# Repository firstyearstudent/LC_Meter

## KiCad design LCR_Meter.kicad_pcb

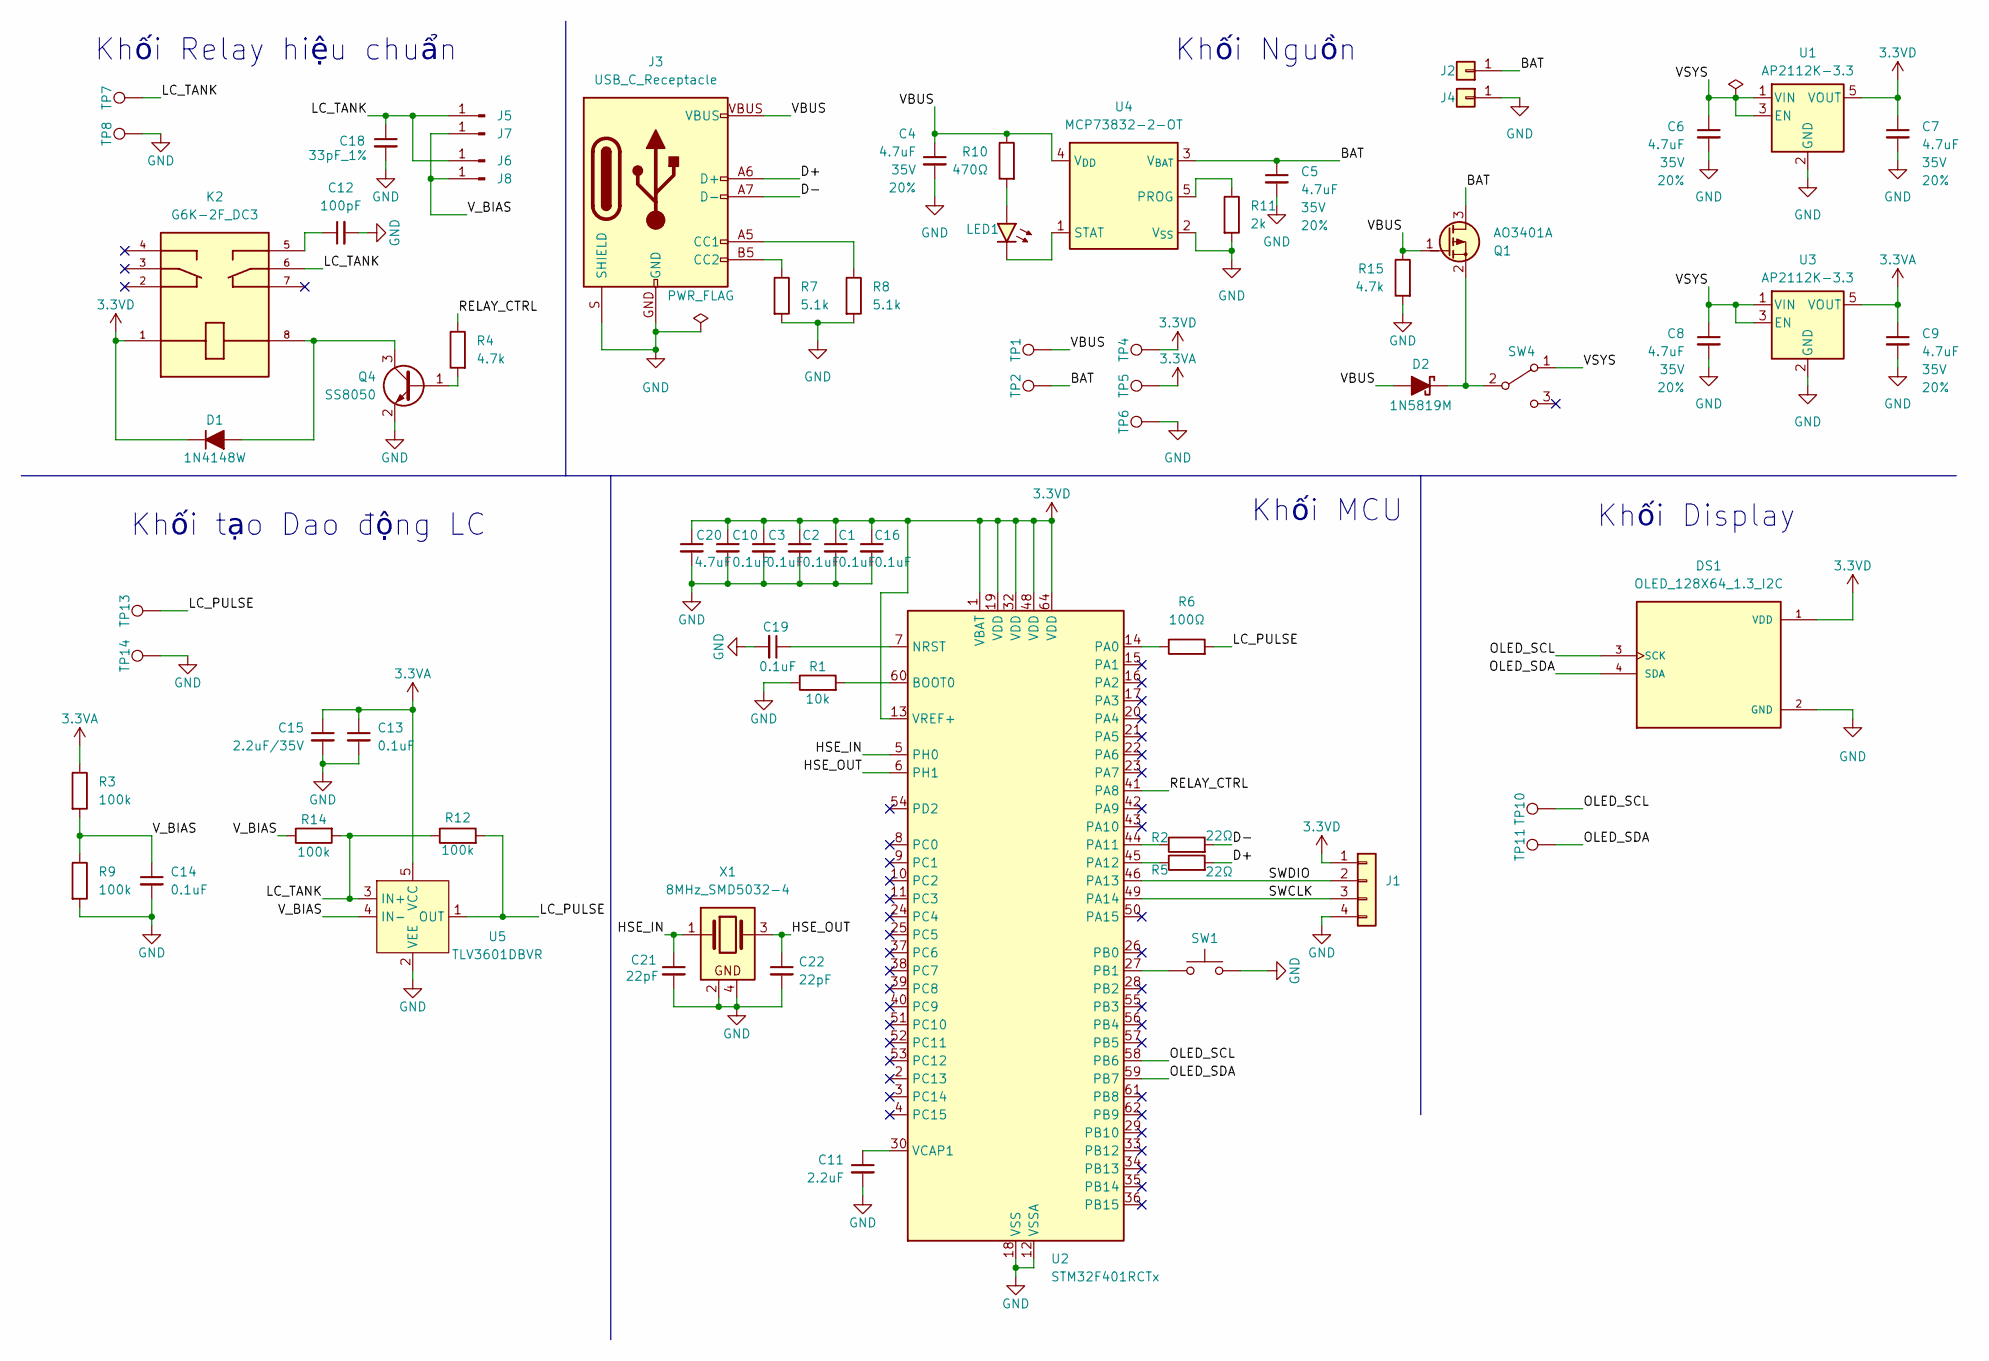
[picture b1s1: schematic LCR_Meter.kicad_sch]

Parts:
C1, C2, C3, C10, C13, C14, C16, C19: 100nF_0603_16V; C_0603; Part Number 0603YC104KAT2A; JLCPCB ID C14663
C4, C5, C6, C7, C8, C9: 4.7uF; C_0603_1608Metric; Voltage 35V; Tolerance 20%
C11: 2.2uF_0603_25V; C_0603; Part Number GRM188R6YA225KA12D; JLCPCB ID C57895
C12: 100pF_1%; C_0603; Part Number CC0603JRNPO9BN101; JLCPCB ID C14858
C15: 2.2uF_0805_35V; C_0805; Part Number GRT21BC8YA225KE13L; JLCPCB ID C49217
C18: 33pF_1%; C_0603_1608Metric
C20: 4.7uF_0603_10V; C_0603; Part Number CL10A475KP8NNNC; JLCPCB ID C1705
C21, C22: 22pF; C_0402_1005Metric
D1: 1N4148W; D_SOD-123
D2: 1N5819M; D_MELF
DS1: OLED_128X64_1.3_I2C; LCD_OLED_128X64_1.3_I2C; PARTREV NA
J1: PinHeader_1x04_P2.54mm_Vertical; Part Number TBD
J2, J4: Conn_01x01; SolderWire-0.75sqmm_1x01_D1.25mm_OD2.3mm
J3: USB_C_Receptacle; USB-C_16
J5, J7: Conn_01x01_Pin; SolderWirePad_1x01_SMD_2x4mm
J6, J8: Conn_01x01_Pin; Banana_Jack_1Pin
K2: G6K-2F_DC3; RELAY_G6K-2F_DC3; PARTREV K106-E1-11
LED1: LED_0805_Red; LED_0805_2012Metric
Q1: AO3401A; SOT-23
Q4: SS8050; SOT-23
R1: 10k_0603; R_0603; Part Number RC0603FR-0710KL; JLCPCB ID C25804
R2, R5: 22Ω_0603; R_0603; Part Number 0603WAF220JT5E; JLCPCB ID C23345
R3, R9, R12, R14: 100k_0805; R_0805_2012Metric; Part Number 0805W8F1003T5E; JLCPCB ID C149504
R4, R15: 4.7k_0805; R_0805_2012Metric; Part Number RT0805FRE074K7L
R6: 100R_0603; R_0603; Part Number RC0603FR-07100RL; JLCPCB ID C22775
R7, R8: 5.1k_0805; R_0805_2012Metric; Part Number 0805W8F5101T5E; JLCPCB ID C27834
R10: 470Ω_0603; R_0603; Part Number 0603WAF4700T5E; JLCPCB ID C23179
R11: 2k_0805; R_0805_2012Metric; Part Number 0805W8F2001T5E; JLCPCB ID C17604
SW1: Switch_Tactile_CnK; Button_CnK_PTS636.0_6x3.5mm
SW4: Switch_Slide_Top_CnK_JS102011SCQN_8.5x3.5mm
TP1, TP2, TP4, TP5, TP6, TP7, TP8, TP10, TP11, TP13, TP14: 0.75mm; TestPoint-0.75mm
U1, U3: AP2112K-3.3; SOT-23-5
U2: STM32F401RCTx; LQFP-64_10x10mm_P0.5mm
U4: MCP73832-2-OT; SOT-23-5
U5: TLV3601DBVR; Comparator_Texas_TLV3601DBVR
X1: 8MHz_SMD5032-4; Crystal_SMD_5032-4Pin_5.0x3.2mm

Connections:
3.3VA: C9.1, C13.1, C15.1, R3.1, TP5.1 (1_1), U3.5 (VOUT), U5.5 (VCC)
3.3VD: C1.1, C2.1, C3.1, C7.1, C10.1, C16.1, C20.1, D1.1 (K), DS1.1 (VDD), J1.1, K2.1, TP4.1 (1_1), U1.5 (VOUT), U2.1 (VBAT), U2.13 (VREF+), U2.19 (VDD), U2.32 (VDD), U2.48 (VDD), U2.64 (VDD)
/BAT: C5.1, J2.1 (Pin_1_1), Q1.3 (D), TP2.1 (1_1), U4.3 (V_{BAT})
/D+: J3.A6 (D+), J3.B6 (D+), R5.2
/D-: J3.A7 (D-), J3.B7 (D-), R2.2
/HSE_IN: C21.1, U2.5 (PH0), X1.1
/HSE_OUT: C22.1, U2.6 (PH1), X1.3
/LC_PULSE: R6.2, R12.2, TP13.1 (1_1), U5.1 (OUT)
/LC_TANK: C18.1, J5.1 (Pin_1_1), J6.1 (Pin_1_1), K2.6, R12.1, R14.2, TP7.1 (1_1), U5.3 (IN+)
/OLED_SCL: DS1.3 (SCK), TP10.1, U2.58 (PB6)
/OLED_SDA: DS1.4 (SDA), TP11.1, U2.59 (PB7)
/RELAY_CTRL: R4.1, U2.41 (PA8)
/SWCLK: J1.3, U2.49 (PA14)
/SWDIO: J1.2, U2.46 (PA13)
/VBUS: C4.1, D2.2 (A), J3.VBUS, Q1.1 (G), R10.1, R15.1, TP1.1 (1_1), U4.4 (V_{DD})
/VSYS: C6.1, C8.1, SW4.1 (A), U1.1 (VIN), U1.3 (EN), U3.1 (VIN), U3.3 (EN)
/V_BIAS: C14.1, J7.1 (Pin_1_1), J8.1 (Pin_1_1), R3.2, R9.1, R14.1, U5.4 (IN-)
GND: C1.2, C2.2, C3.2, C4.2, C5.2, C6.2, C7.2, C8.2, C9.2, C10.2, C11.2, C12.2, C13.2, C14.2, C15.2, C16.2, C18.2, C19.2, C20.2, C21.2, C22.2, DS1.2 (GND), J1.4, J3.GND, J3.S (SHIELD), J4.1 (Pin_1_1), Q4.2 (E), R1.1, R7.2, R8.2, R9.2, R11.2, R15.2, SW1.2, TP6.1 (1_1), TP8.1 (1_1), TP14.1, U1.2 (GND), U2.12 (VSSA), U2.18 (VSS), U2.31 (VSS), U2.47 (VSS), U2.63 (VSS), U3.2 (GND), U4.2 (V_{SS}), U5.2 (VEE), X1.2, X1.4
unnamed: C12.1, K2.5
unnamed: D1.2 (A), K2.8, Q4.3 (C)
unnamed: D2.1 (K), Q1.2 (S), SW4.2 (B)
unnamed: J3.A5 (CC1), R8.1
unnamed: J3.B5 (CC2), R7.1
unnamed: LED1.2 (A), R10.2
unnamed: LED1.1 (K), U4.1 (STAT)
unnamed: Q4.1 (B), R4.2
unnamed: R1.2, U2.60 (BOOT0)
unnamed: C19.1, U2.7 (NRST)
unnamed: R6.1, U2.14 (PA0)
unnamed: R2.1, U2.44 (PA11)
unnamed: R5.1, U2.45 (PA12)
unnamed: SW1.1, U2.27 (PB1)
unnamed: C11.1, U2.30 (VCAP1)
unnamed: R11.1, U4.5 (PROG)

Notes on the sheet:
Khối Relay hiệu chuẩn
Khối Display
Khối Nguồn
Khối MCU
Khối tạo Dao động LC

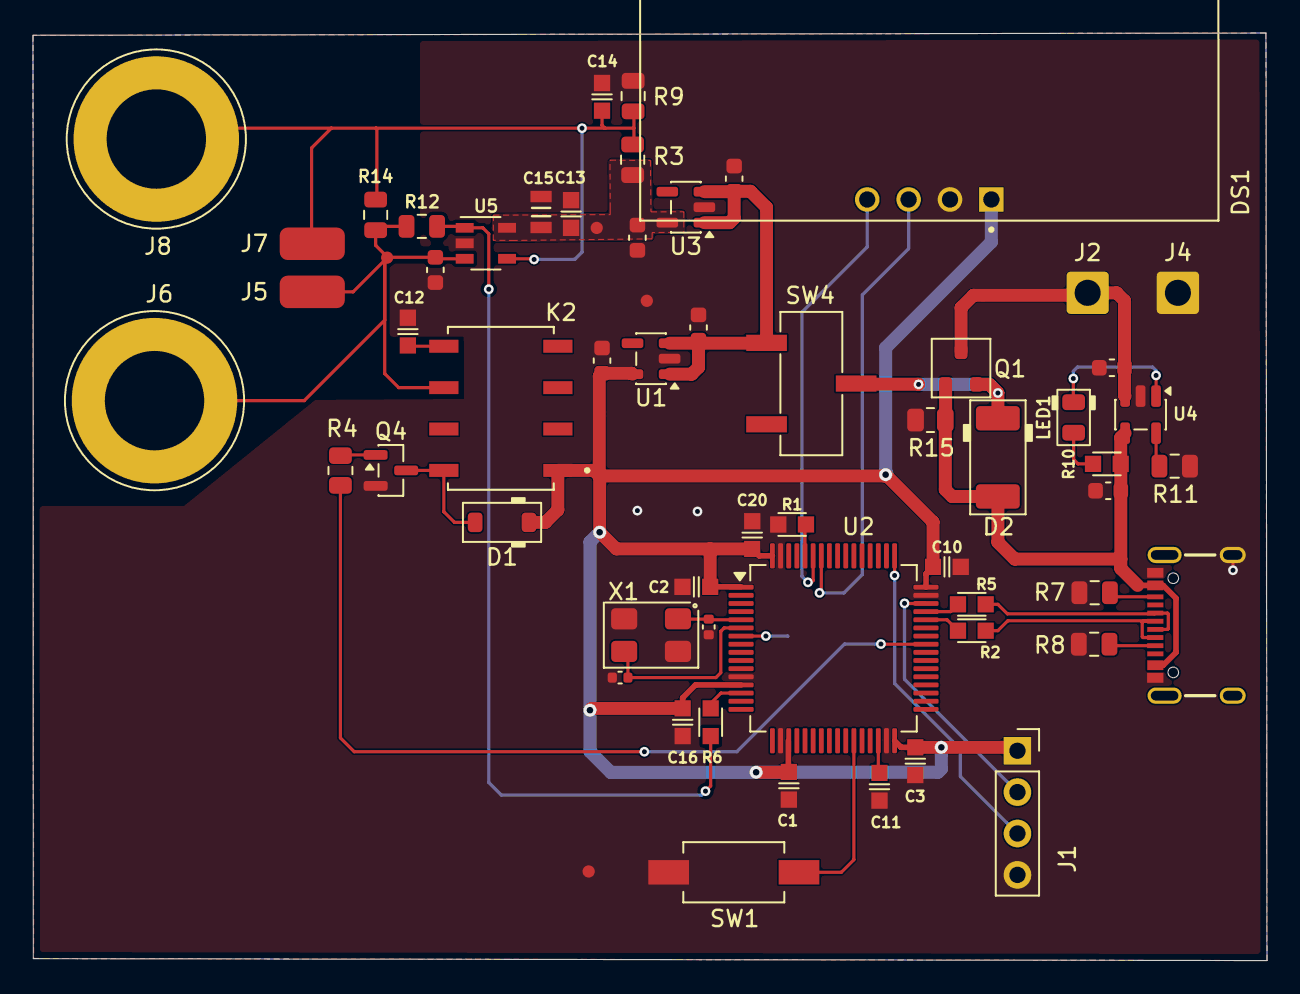
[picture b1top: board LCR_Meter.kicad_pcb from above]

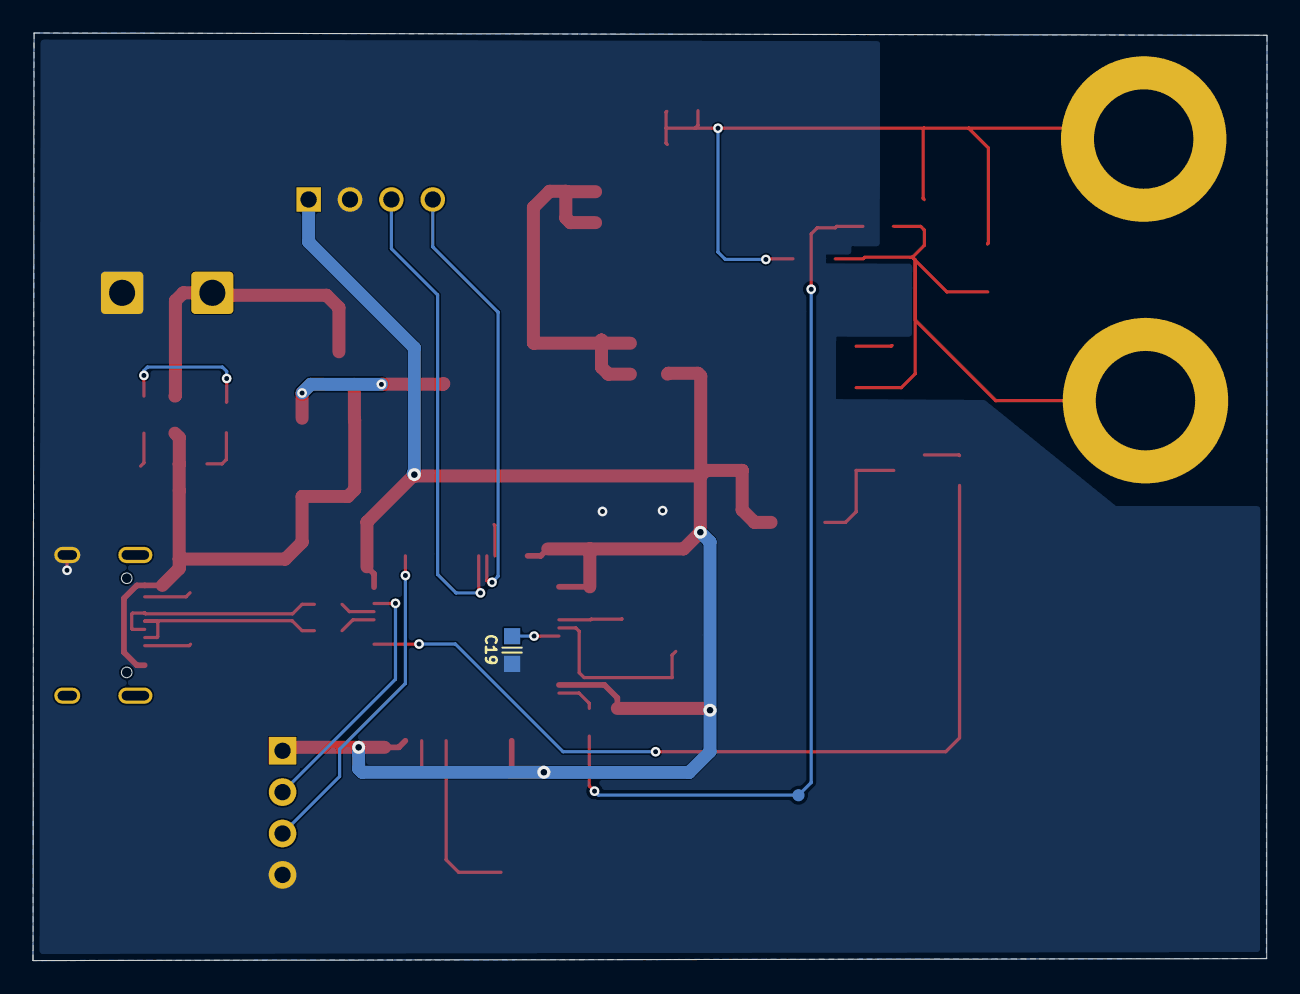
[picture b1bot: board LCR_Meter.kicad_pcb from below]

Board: 2 copper layers, 75.8 x 56.9 mm, 66 parts (2 on the bottom side), 34 nets.

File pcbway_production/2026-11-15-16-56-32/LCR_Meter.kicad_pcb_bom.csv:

Designator,Quantity,Value,Footprint,Package,MPN,DNP,Mount_Type,Description,Specifications,Manufacturer,Display,JLCPCB ID,Production Stage,PROD_ID,Voltage,Tolerance,MF,Price,Check_prices,STANDARD,PARTREV,SnapEDA_Link,MP,Availability,MANUFACTURER,KiLib_Generator,MAXIMUM_PACKAGE_HEIGHT,Sim.Device,Sim.Pins
"C1, C10, C13, C14, C16, C19, C2, C3",8,100nF_0603_16V,C_0603,,0603YC104KAT2A,,smt,"0.1uF, Min. 16V 10%, X7R or X5R or similar","0.1uF, Min. 16V 10%, X7R or X5R or similar",AVX Corporation,0.1uF,C14663,A,,,,,,,,,,,,,,,,
C11,1,2.2uF_0603_25V,C_0603,,GRM188R6YA225KA12D,,smt,"2.2uF, Min 25V 10% X5R","2.2uF, Min 25V 10% X5R",Murata,2.2uF,C57895,A,,,,,,,,,,,,,,,,
C12,1,100pF_1%,C_0603,,CC0603JRNPO9BN101,,smt,"100pF, Min. 50V 10%, NP0","100pF, Min. 50V 10% NP0 or C0G",Yageo,100pF,C14858,A,,,,,,,,,,,,,,,,
C15,1,2.2uF_0805_35V,C_0805,,GRT21BC8YA225KE13L,,smt,"2.2uF, 35V 10% X6S , 0805","2.2uF, 35V 10% X6S , 0805",Murata,2.2uF/35V,C49217,A,,,,,,,,,,,,,,,,
C18,1,33pF_1%,C_0603_1608Metric,,,,smt,Unpolarized capacitor,,,,,,CAP-10142,,,,,,,,,,,,,,,
C20,1,4.7uF_0603_10V,C_0603,,CL10A475KP8NNNC,,smt,"4.7uF, Min. 10V 10%, X5R or similar",,,4.7uF,C1705,A,,,,,,,,,,,,,,,,
"C21, C22",2,22pF,C_0402_1005Metric,,,,smt,Unpolarized capacitor,,,,,,CAP-25012,,,,,,,,,,,,,,,
"C4, C5, C6, C7, C8, C9",6,4.7uF,C_0603_1608Metric,,,,smt,Unpolarized capacitor,,,,,,CAP-14106,35V,20%,,,,,,,,,,,,,
D1,1,1N4148W,D_SOD-123,,,,smt,"SOD-123 Diode, Small Signal, Fast Switching, 75V, 150mA, 4ns, Alternate KiCad Library",,,,,,,,,,,,,,,,,,,,,
D2,1,1N5819M,D_MELF,,,,smt,"MELF Schottky diode, 40V, 1A, Alternate KiCAD Library",,,,,,,,,,,,,,,,,,,,,
DS1,1,OLED_128X64_1.3_I2C,LCD_OLED_128X64_1.3_I2C,None,,,tht,"Non-Touch Graphic LCD Display Module Transmissive White OLED, Monochrome I2C 1.3 (33.02mm) 128 x 64",,,,,,,,,UNIVERSAL-SOLDER Electronics Ltd,None,https://www.snapeda.com/parts/OLED%20128x64%201.3%22%20I2C/U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,Manufacturer Recommendations,NA,https://www.snapeda.com/parts/OLED%20128x64%201.3%22%20I2C/U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,OLED 128x64 1.3&quot; I2C,Not in stock,UNIVERSAL-SOLDER Electronics Ltd,,,,
J1,1,~,PinHeader_1x04_P2.54mm_Vertical,,TBD,,tht,HEADER 1x4 MALE PINS 2.54mm VERTICAL TH,HEADER 1x4 MALE PINS 2.54mm VERTICAL TH,TBD,,,B,,,,,,,,,,,,,,,,
"J2, J4",2,Conn_01x01,SolderWire-0.75sqmm_1x01_D1.25mm_OD2.3mm,,,,tht,Large diameter solder lug for power connections to LiPo batteries,,,,,,,,,,,,,,,,,,connector/wire,,,
J3,1,USB_C_Receptacle,USB-C_16,,,,tht,USB 2.0-only Type-C Receptacle connector,,,,,,CONN-14122,,,,,,,,,,,,,,,
"J5, J7",2,Conn_01x01_Pin,SolderWirePad_1x01_SMD_2x4mm,,,,tht,"Generic connector, single row, 01x01, script generated",,,,,,,,,,,,,,,,,,,,,
"J6, J8",2,Conn_01x01_Pin,Banana_Jack_1Pin,,,,tht,"Generic connector, single row, 01x01, script generated",,,,,,,,,,,,,,,,,,,,,
K2,1,G6K-2F_DC3,RELAY_G6K-2F_DC3,TDFN-6 Omron Electronics,,,smt,Telecom Relay DPDT (2 Form C) Surface Mount,,,,,,,,,Omron Electronics,None,https://www.snapeda.com/parts/G6K-2F%20DC3/Omron/view-part/?ref=eda,Manufacturer Recommendations,K106-E1-11,https://www.snapeda.com/parts/G6K-2F%20DC3/Omron/view-part/?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,G6K-2F DC3,In Stock,Omron Electronics Inc-EMC Div,,5.7 mm,,
LED1,1,LED_0805_Red,LED_0805_2012Metric,,,,smt,"Red SMD LED, 0805, Alternate KiCad Library",,,,,,,,,,,,,,,,,,,,,
Q1,1,AO3401A,SOT-23,,,,smt,"SOT-23 P-MOSFET enchancement mode transistor, 30V, 4A, 1.4W, Alternate KiCAD Library",,,,,,,,,,,,,,,,,,,,,
Q4,1,SS8050,SOT-23,,,,smt,"General Purpose NPN Transistor, 1.5A Ic, 25V Vce, SOT-23",,,,,,,,,,,,,,,,,,package/gullwing,,NPN,1=B 2=E 3=C
R1,1,10k_0603,R_0603,,RC0603FR-0710KL,,smt,"10K, 1%, 1/10W, 0603","10K, 1%, 1/10W, 0603",Yageo,10k,C25804,,,,,,,,,,,,,,,,,
R10,1,470Ω_0603,R_0603,,0603WAF4700T5E,,smt,"470Ω, 1%, 1/10W, 0603","470Ω, 1%, 1/10W, 0603",UNI-ROYAL,470Ω,C23179,A,,,,,,,,,,,,,,,,
R11,1,2k_0805,R_0805_2012Metric,,0805W8F2001T5E,,smt,"2k, 1%, 1/8W, 0805","2k, 1%, 1/8W, 0805",UNI-ROYAL,2k,C17604,A,,,,,,,,,,,,,,,,
"R12, R14, R3, R9",4,100k_0805,R_0805_2012Metric,,0805W8F1003T5E,,smt,"100k, 1%, 1/8W, 0805","100k, 1%, 1/8W, 0805",UNI-ROYAL,100k,C149504,A,,,,,,,,,,,,,,,,
"R15, R4",2,4.7k_0805,R_0805_2012Metric,,RT0805FRE074K7L ,,smt,"4.7k, 1/8W, 1%","4.7k, 1/8W, 1%",Yageo,4.7k,,,,,,,,,,,,,,,SMD_2terminal_chip_molded,,,
"R2, R5",2,22Ω_0603,R_0603,,0603WAF220JT5E,,smt,"22Ω, 1%, 1/10W, 0603","22Ω, 1%, 1/10W, 0603",UNI-ROYAL,22Ω,C23345,A,,,,,,,,,,,,,,,,
R6,1,100R_0603,R_0603,,RC0603FR-07100RL,,smt,"100Ω, 1%, 1/10W, 0603","100Ω, 1%, 1/10W, 0603",Yageo,100Ω,C22775,,,,,,,,,,,,,,,,,
"R7, R8",2,5.1k_0805,R_0805_2012Metric,,0805W8F5101T5E,,smt,"5.1k, 1%, 1/8W, 0805","5.1k, 1%, 1/8W, 0805",UNI-ROYAL,5.1k,C27834,A,,,,,,,,,,,,,,,,
SW1,1,Switch_Tactile_CnK,Button_CnK_PTS636.0_6x3.5mm,,,,smt,"Push button switch, C&K PTS636 SM25F SMTR LFS, Tactile Switch SPST-NO Top Actuated Surface Mount",,,,,,,,,,,,,,,,,,,,,
SW4,1,~,Switch_Slide_Top_CnK_JS102011SCQN_8.5x3.5mm,,,,smt,"Slide Switch SPDT Surface Mount, Right Angle",,,,,,,,,,,,,,,,,,,,,
"TP1, TP10, TP11, TP13, TP2, TP4, TP5, TP6, TP7, TP8",10,0.75mm,TestPoint-0.75mm,,,,tht,Test Point,,,,,,,,,,,,,,,,,,,,,
"U1, U3",2,AP2112K-3.3,SOT-23-5,,,,smt,"600mA low dropout linear regulator, with enable pin, 3.8V-6V input voltage range, 3.3V fixed positive output, SOT-23-5",,,,,,,,,,,,,,,,,,package/gullwing,,,
U2,1,STM32F401RCTx,LQFP-64_10x10mm_P0.5mm,,,,smt,"STMicroelectronics Arm Cortex-M4 MCU, 256KB flash, 64KB RAM, 84 MHz, 1.7-3.6V, 50 GPIO, LQFP64",,,,,,,,,,,,,,,,,,package/gullwing,,,
U4,1,MCP73832-2-OT,SOT-23-5,,,,smt,"Single cell, Li-Ion/Li-Po charge management controller, 4.20V, Open-Drain Status Output, in SOT23-5 package",,,,,,,,,,,,,,,,,,package/gullwing,,,
U5,1,TLV3601DBVR,Comparator_Texas_TLV3601DBVR,,,,smt,"Comparator General Purpose CMOS, Push-Pull, Rail-to-Rail SOT-23-5",,,,,,,,,,,,,,,,,,,,,
X1,1,8MHz_SMD5032-4,Crystal_SMD_5032-4Pin_5.0x3.2mm,,,,smt,"SMD Quartz crystal, 4 terminals, 5.0mm x 3.2mm, Alternate KiCad Library",,,,,,,,,,,,,,,,,,,,,
